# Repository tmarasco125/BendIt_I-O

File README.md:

# Bendit_I/O: A Framework for Networked Performance of Circuit-Bent Devices
Under Development, more infor available in July 2020.

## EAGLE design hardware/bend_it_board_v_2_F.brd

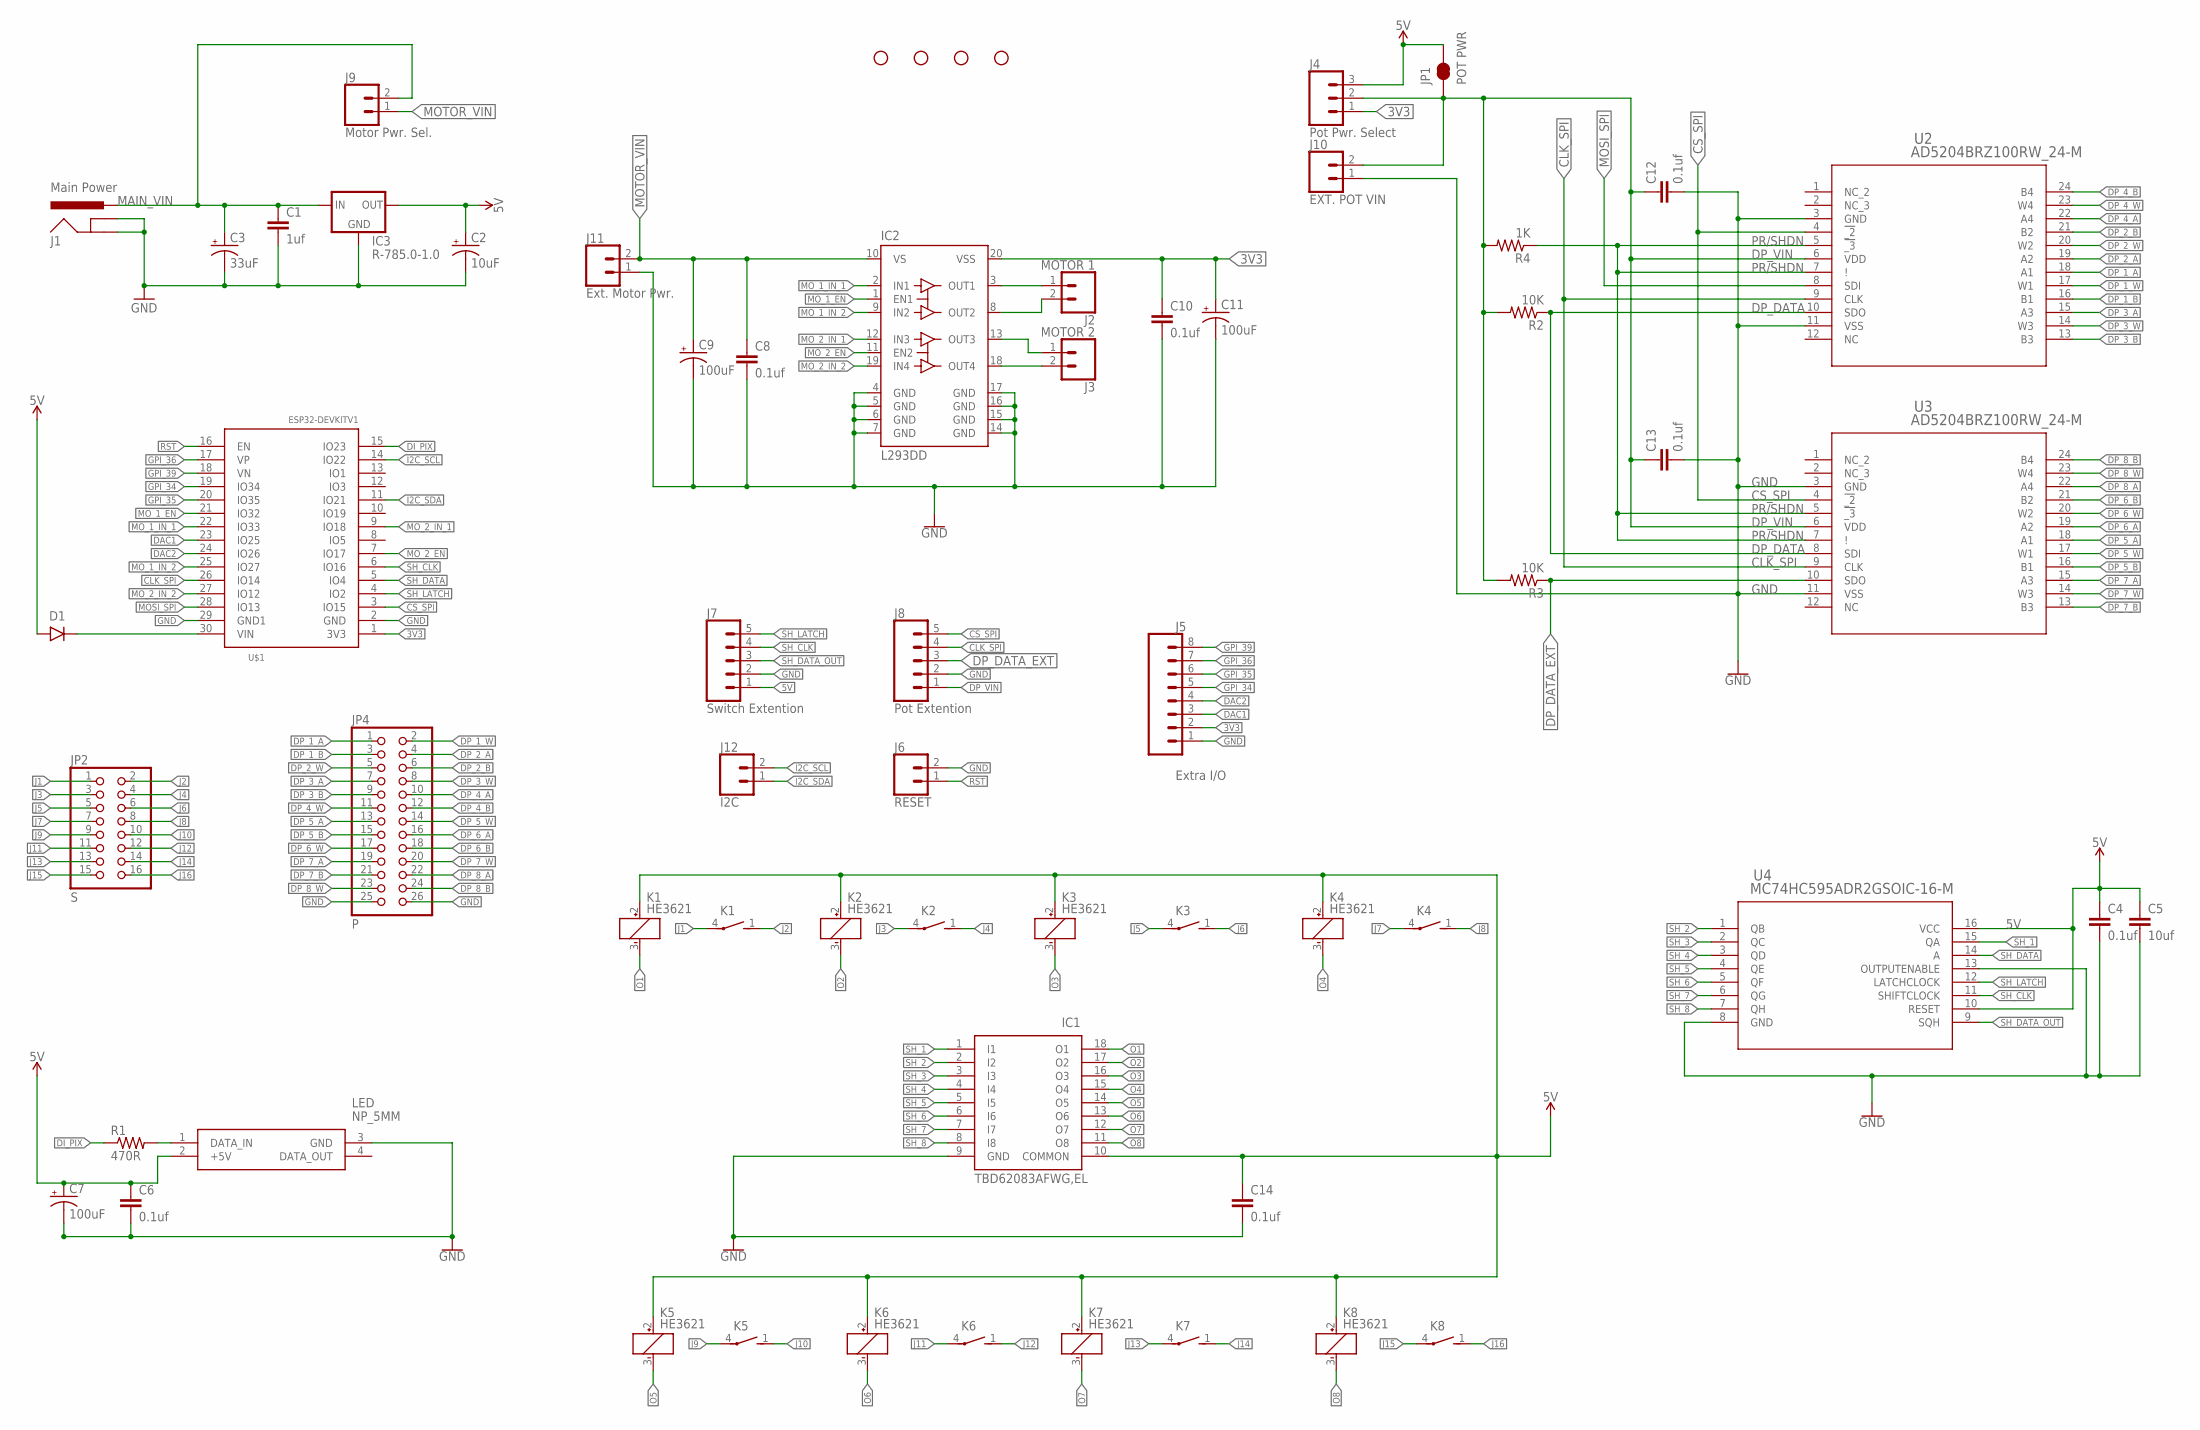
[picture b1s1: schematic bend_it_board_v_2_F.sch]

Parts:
C1: 1uf; C0805
C2: 10uF; PANASONIC_B
C3: 33uF; PANASONIC_D
C4, C6, C8, C10, C12, C13, C14: 0.1uf; C0805
C5: 10uf; C0805
C7, C9, C11: 100uF; PANASONIC_D
D1: 1N4001; DO41-10
H1, H2, H3, H4: STAND-OFF
IC1: TBD62083AFWG,EL; SOIC127P1032X285-18N
IC2: L293DD; SO20
IC3: R-785.0-1.0; SIP3
J1: Main Power; POWER_JACK_PTH
J2: MOTOR 1; SCREWTERMINAL-5MM-2
J3: MOTOR 2; SCREWTERMINAL-5MM-2
J4: Pot Pwr. Select; 1X03
J5: Extra I/O; 1X08
J6: RESET; 1X02
J7: Switch Extention; 1X05
J8: Pot Extention; 1X05
J9: Motor Pwr. Sel.; 1X02
J10: EXT. POT VIN; 1X02_LOCK_LONGPADS
J11: Ext. Motor Pwr.; 1X02_LOCK_LONGPADS
J12: I2C; 1X02
JP1: POT PWR; SMT-JUMPER_2_NC_TRACE_SILK
JP2: S; 2X08
JP4: P; 2X13
K1, K2, K3, K4, K5, K6, K7, K8: HE3621
LED: NP_5MM; 1938
R1: 470R; R0805
R2, R3: 10K; R0805
R4: 1K; R0805
U2, U3: AD5204BRZ100RW_24-M; RW_24-M
U4: MC74HC595ADR2GSOIC-16-M; SOIC-16-M
U$1: ESP32DEVKITV1; ESP32-DEVKITV1

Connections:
3V3: C10.1, C11.+, IC2.20 (VSS), J4.1, J5.2, U$1.1 (3V3)
5V: C2.+, C4.1, C5.1, C6.1, C7.+, C14.1, D1.A (ANODE), IC1.10 (COMMON), IC3.3 (OUT), J4.3, J7.1, JP1.2, K1.2 (+), K2.2 (+), K3.2 (+), K4.2 (+), K5.2 (+), K6.2 (+), K7.2 (+), K8.2 (+), LED.2 (+5V), U4.10 (RESET), U4.16 (VCC)
CLK_SPI: J8.4, U2.9 (CLK), U3.9 (CLK), U$1.26 (IO14)
CS_SPI: J8.5, U2.4 (!_2), U3.4 (!_2), U$1.3 (IO15)
DAC1: J5.3, U$1.23 (IO25)
DAC2: J5.4, U$1.24 (IO26)
DI_PIX: R1.1, U$1.15 (IO23)
DP_1_A: JP4.1, U2.18 (A1)
DP_1_B: JP4.3, U2.16 (B1)
DP_1_W: JP4.2, U2.17 (W1)
DP_2_A: JP4.4, U2.19 (A2)
DP_2_B: JP4.6, U2.21 (B2)
DP_2_W: JP4.5, U2.20 (W2)
DP_3_A: JP4.7, U2.15 (A3)
DP_3_B: JP4.9, U2.13 (B3)
DP_3_W: JP4.8, U2.14 (W3)
DP_4_A: JP4.10, U2.22 (A4)
DP_4_B: JP4.12, U2.24 (B4)
DP_4_W: JP4.11, U2.23 (W4)
DP_5_A: JP4.13, U3.18 (A1)
DP_5_B: JP4.15, U3.16 (B1)
DP_5_W: JP4.14, U3.17 (W1)
DP_6_A: JP4.16, U3.19 (A2)
DP_6_B: JP4.18, U3.21 (B2)
DP_6_W: JP4.17, U3.20 (W2)
DP_7_A: JP4.19, U3.15 (A3)
DP_7_B: JP4.21, U3.13 (B3)
DP_7_W: JP4.20, U3.14 (W3)
DP_8_A: JP4.22, U3.22 (A4)
DP_8_B: JP4.24, U3.24 (B4)
DP_8_W: JP4.23, U3.23 (W4)
DP_DATA: R2.1, U2.10 (SDO), U3.8 (SDI)
DP_DATA_EXT: J8.3, R3.1, U3.10 (SDO)
DP_VIN: C12.1, C13.1, J4.2, J8.1, J10.2, JP1.1, R2.2, R3.2, R4.2, U2.6 (VDD), U3.6 (VDD)
GND: C1.2, C2.-, C3.-, C4.2, C5.2, C6.2, C7.-, C8.2, C9.-, C10.2, C11.-, C12.2, C13.2, C14.2, IC1.9 (GND), IC2.4 (GND), IC2.5 (GND), IC2.6 (GND), IC2.7 (GND), IC2.14 (GND), IC2.15 (GND), IC2.16 (GND), IC2.17 (GND), IC3.2 (GND), J1.GND, J1.GNDBREAK, J5.1, J6.2, J7.2, J8.2, J10.1, J11.1, JP4.25, JP4.26, LED.3 (GND), U2.3 (GND), U2.11 (VSS), U3.3 (GND), U3.11 (VSS), U4.8 (GND), U4.13 (OUTPUTENABLE), U$1.2 (GND), U$1.29 (GND1)
GPI_34: J5.5, U$1.19 (IO34)
GPI_35: J5.6, U$1.20 (IO35)
GPI_36: J5.7, U$1.17 (VP)
GPI_39: J5.8, U$1.18 (VN)
I2C_SCL: J12.2, U$1.14 (IO22)
I2C_SDA: J12.1, U$1.11 (IO21)
J1: JP2.1, K1.4
J2: JP2.2, K1.1 (S)
J3: JP2.3, K2.4
J4: JP2.4, K2.1 (S)
J5: JP2.5, K3.4
J6: JP2.6, K3.1 (S)
J7: JP2.7, K4.4
J8: JP2.8, K4.1 (S)
J9: JP2.9, K5.4
J10: JP2.10, K5.1 (S)
J11: JP2.11, K6.4
J12: JP2.12, K6.1 (S)
J13: JP2.13, K7.4
J14: JP2.14, K7.1 (S)
J15: JP2.15, K8.4
J16: JP2.16, K8.1 (S)
MAIN_VIN: C1.1, C3.+, IC3.1 (IN), J1.PWR, J9.2
MOSI_SPI: U2.8 (SDI), U$1.28 (IO13)
MOTOR_1_OUT: IC2.3 (OUT1), J2.1
MOTOR_2_OUT: IC2.8 (OUT2), J2.2
MOTOR_3_OUT: IC2.13 (OUT3), J3.1
MOTOR_4_OUT: IC2.18 (OUT4), J3.2
MOTOR_VIN: C8.1, C9.+, IC2.10 (VS), J9.1, J11.2
MO_1_EN: IC2.1 (EN1), U$1.21 (IO32)
MO_1_IN_1: IC2.2 (IN1), U$1.22 (IO33)
MO_1_IN_2: IC2.9 (IN2), U$1.25 (IO27)
MO_2_EN: IC2.11 (EN2), U$1.7 (IO17)
MO_2_IN_1: IC2.12 (IN3), U$1.9 (IO18)
MO_2_IN_2: IC2.19 (IN4), U$1.27 (IO12)
unnamed: D1.C (CATHODE), U$1.30 (VIN)
unnamed: LED.1 (DATA_IN), R1.2
O1: IC1.18 (O1), K1.3 (-)
O2: IC1.17 (O2), K2.3 (-)
O3: IC1.16 (O3), K3.3 (-)
O4: IC1.15 (O4), K4.3 (-)
O5: IC1.14 (O5), K5.3 (-)
O6: IC1.13 (O6), K6.3 (-)
O7: IC1.12 (O7), K7.3 (-)
O8: IC1.11 (O8), K8.3 (-)
PR/SHDN: R4.1, U2.5 (!_3), U2.7 (!), U3.5 (!_3), U3.7 (!)
RST: J6.1, U$1.16 (EN)
SH_1: IC1.1 (I1), U4.15 (QA)
SH_2: IC1.2 (I2), U4.1 (QB)
SH_3: IC1.3 (I3), U4.2 (QC)
SH_4: IC1.4 (I4), U4.3 (QD)
SH_5: IC1.5 (I5), U4.4 (QE)
SH_6: IC1.6 (I6), U4.5 (QF)
SH_7: IC1.7 (I7), U4.6 (QG)
SH_8: IC1.8 (I8), U4.7 (QH)
SH_CLK: J7.4, U4.11 (SHIFTCLOCK), U$1.6 (IO16)
SH_DATA: U4.14 (A), U$1.5 (IO4)
SH_DATA_OUT: J7.3, U4.9 (SQH)
SH_LATCH: J7.5, U4.12 (LATCHCLOCK), U$1.4 (IO2)

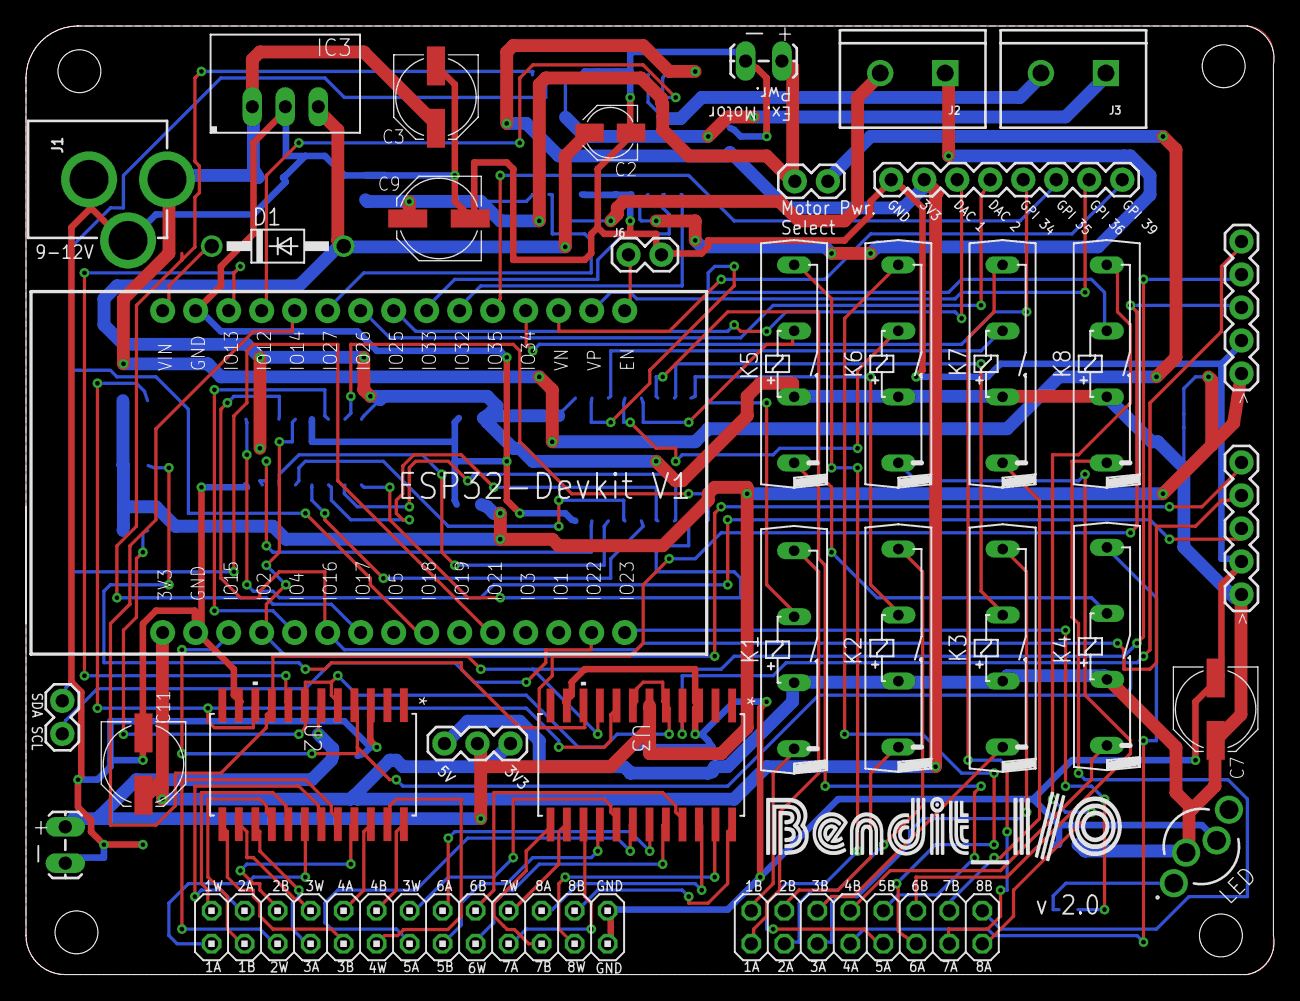
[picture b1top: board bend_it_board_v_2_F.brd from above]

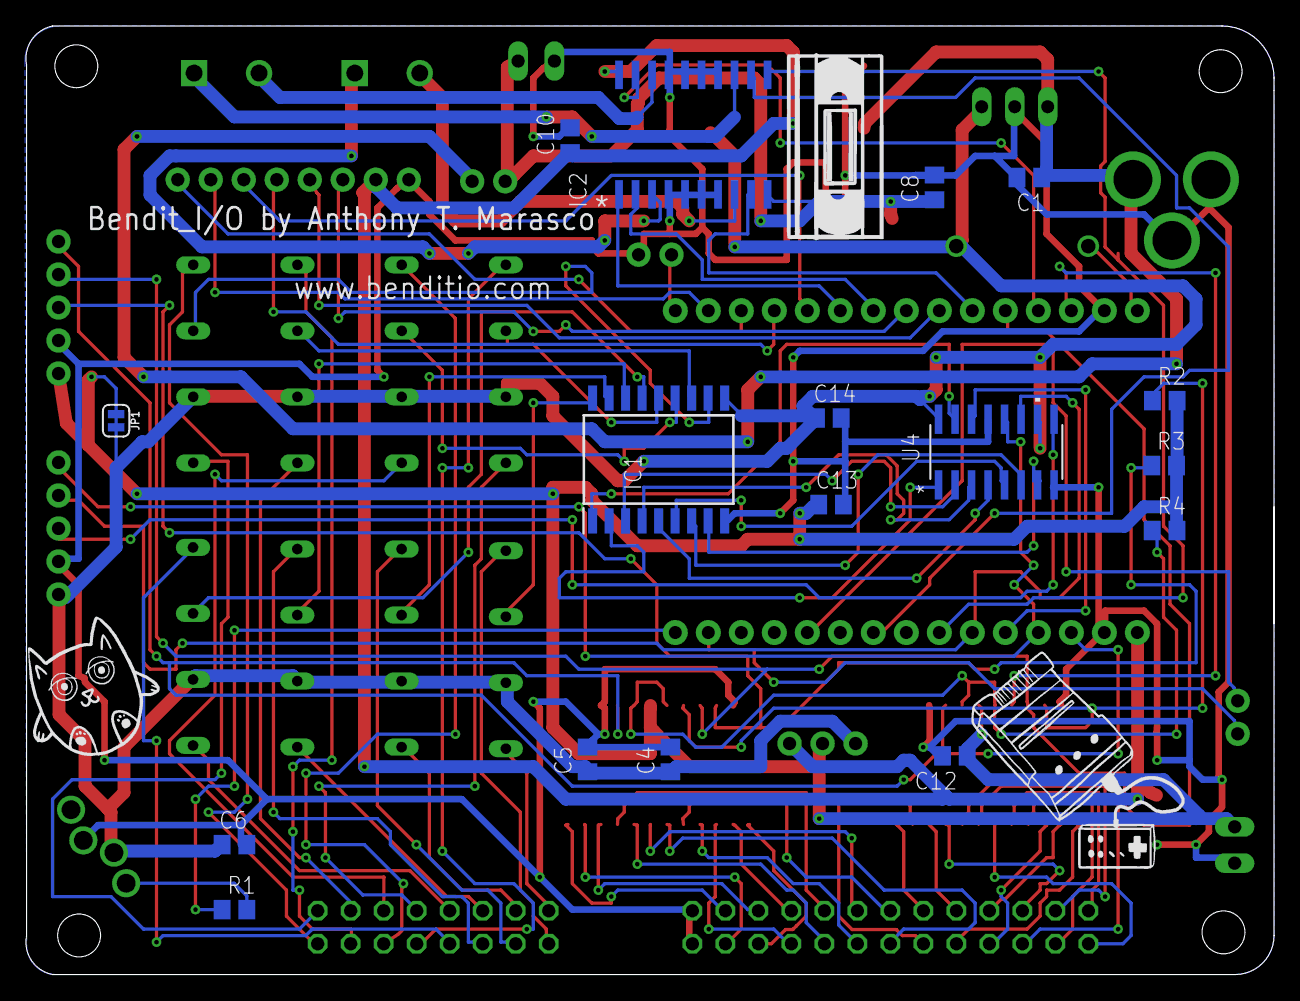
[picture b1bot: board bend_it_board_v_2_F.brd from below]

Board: 2 copper layers, 96.0 x 73.0 mm, 54 parts (17 on the bottom side), 94 nets.

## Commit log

2018-11-16 Update of Arduino and server code
2019-02-21 Alpha state changes: individual device communication
2019-03-09 Changes to web interface/server data passing structure
2019-03-09 Updates to repo name/file name changes
2019-03-09 cleaned board code
2019-07-02 changes for gravity|density performance
2020-03-02 making new brach
    Making new branch module_dev
2020-03-03 boards can connect using benditHub
2020-03-04 building out benditBroswer and benditHub
2020-03-04 Added pot, motor, switch classes to benditBroswer
2020-03-04 building out classes and methods benditBrowser
2020-03-06 no major changes
2020-03-09 created new moduel exports(.Connect, .Device)
2020-03-12 Exporting more classes
2020-03-20 modified BenditDevice class and Bendit class
2020-03-20 Added 'hardware' folder and files
2020-03-20 Updated hardware files to rev F
2020-03-24 BenditDevice can take JSON and args
2020-03-24 updated both 'benditBrowser.js' files
2020-04-02 adding extensions
2020-04-02 flipSwitch() method changes
2020-04-06 updates to switch/pot/motor classes
2020-04-06 adding motor methods
2020-04-08 cleaning
2020-04-08 need to fix setDeviceColor/Number on board code!
2020-04-09 changed handshake event
2020-04-09 edits to server hub
2020-04-09 added to benditHub.js
2020-04-09 working switch_engage event on board code
2020-04-10 Adding web user polling methods
2020-04-14 Adding JSDocs documentation to benditBrowser.js
2020-04-14 changing lexicon on server ("device" to "board")
2020-04-15 Added API documentation pages
2020-04-15 more documentation
2020-04-16 added Motor methods
2020-04-17 documentation changes
2020-04-18 Made socket properties read-only
2020-04-28 Adding examples and updates
2020-04-28 Clean up
2020-04-29 Ready for merge
2020-06-20 updated V1.0 bendit board firmware
2020-07-02 added tutorial text
2020-07-15 Remade Docs
2020-07-15 Remake Docs
2020-07-15 Remake Docs and Tutorials
2020-07-15 New tuts
2020-07-15 Updating Server Example
2020-07-15 Adding new tutorials
2020-07-15 doc logo swap
2020-07-16 Fix logo?
2020-07-16 fix logo
2020-07-17 fixed logo on docs
2020-07-19 Changes for NIME workshop
2020-07-19 Changed board code for NIME 2020
2020-07-19 Added message channels from boards to clients
2020-07-20 Updating Server
2020-07-20 Updating master lib files and show.html
2020-07-20 Updating docs and tutorials
2020-07-21 Update LICENSE
2020-07-21 new docs
2020-07-21 Adding licenses
2020-07-21 Updated tuts
2020-07-21 Bump lodash from 4.17.15 to 4.17.19 in /performance_interface_example
    Bumps [lodash](https://github.com/lodash/lodash) from 4.17.15 to 4.17.19.
    - [Release notes](https://github.com/lodash/lodash/releases)
    - [Commits](https://github.com/lodash/lodash/compare/4.17.15...4.17.19)
2020-07-21 tutorial change
2020-07-21 Updating tutorial 4
2020-07-25 Changes to performance interface webpage
2020-08-13 Updates to cd control page
2020-08-14 format updates
2020-08-15 update license on docs
2021-01-21 Bump socket.io from 2.1.1 to 2.4.0 in /performance_interface_example
    Bumps [socket.io](https://github.com/socketio/socket.io) from 2.1.1 to 2.4.0.
    - [Release notes](https://github.com/socketio/socket.io/releases)
    - [Changelog](https://github.com/socketio/socket.io/blob/2.4.0/CHANGELOG.md)
    - [Commits](https://github.com/socketio/socket.io/compare/2.1.1...2.4.0)
2021-03-03 Updates to baord to server messaging
2021-03-03 update server software version number
2021-03-03 update benditHub.js version number
2021-03-03 quick fix
2021-03-03 editing controller page
2021-03-03 added board message watcher to controller page
2021-03-03 making both CD controller pages match
2021-03-03 only inti devices if boards are connected
2021-03-03 fix on gd.html
2021-03-03 add anonymous function to init devices
2021-03-03 try anony callback again
2021-03-03 add callback functionality to getConnectedBB
2021-03-03 fix callback in benditbrowser.js
2021-03-03 update callback
2021-03-04 fix interface
2021-05-11 Bump lodash from 4.17.15 to 4.17.21 in /performance_interface_example
    Bumps [lodash](https://github.com/lodash/lodash) from 4.17.15 to 4.17.21.
    - [Release notes](https://github.com/lodash/lodash/releases)
    - [Commits](https://github.com/lodash/lodash/compare/4.17.15...4.17.21)

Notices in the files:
parts and their libraries:
SparkFun-Hardware: Licensing: Creative Commons ShareAlike 4.0 International - https://creativecommons.org/licenses/by-sa/4.0
r-78xx_10: (c) 2015 Samuel Lourenço
